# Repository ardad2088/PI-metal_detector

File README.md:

# Pulse Induction (PI) Metal Detector Board

2-layer mixed-signal PCB for a pulse induction metal detector: an STM32 microcontroller, a high-power MOSFET coil driver and an op-amp analog front end.

## How a PI detector works

A pulse induction detector drives its coil with short, strong current pulses and then looks at the signal that decays after each pulse. A metal target changes that decay, and the change is very small, so the receiving circuit has to amplify and condition it carefully before the microcontroller can use it.

## Hardware

| Block | Implementation |
|---|---|
| MCU | STM32F103C8T6 |
| Coil driver | High-power MOSFET switching stage with flyback diode protection for the inductive coil |
| Analog front end | Op-amp stages that amplify and condition the weak target reflection signal |
| Power | Linear regulation with capacitive noise filtering |
| Indicators | Audio and visual indicators |
| PCB | 2 layers, designed in [Altium Designer / KiCad] |

Schematic: [`docs/schematic.pdf`](docs/schematic.pdf) · PCB views: [`docs/pcb_top.png`](docs/pcb_top.png), [`docs/pcb_bottom.png`](docs/pcb_bottom.png)

## Repository layout

```
docs/       photos, schematic PDF, PCB renders
hardware/   KiCad project, libraries, Gerbers, BOM
```

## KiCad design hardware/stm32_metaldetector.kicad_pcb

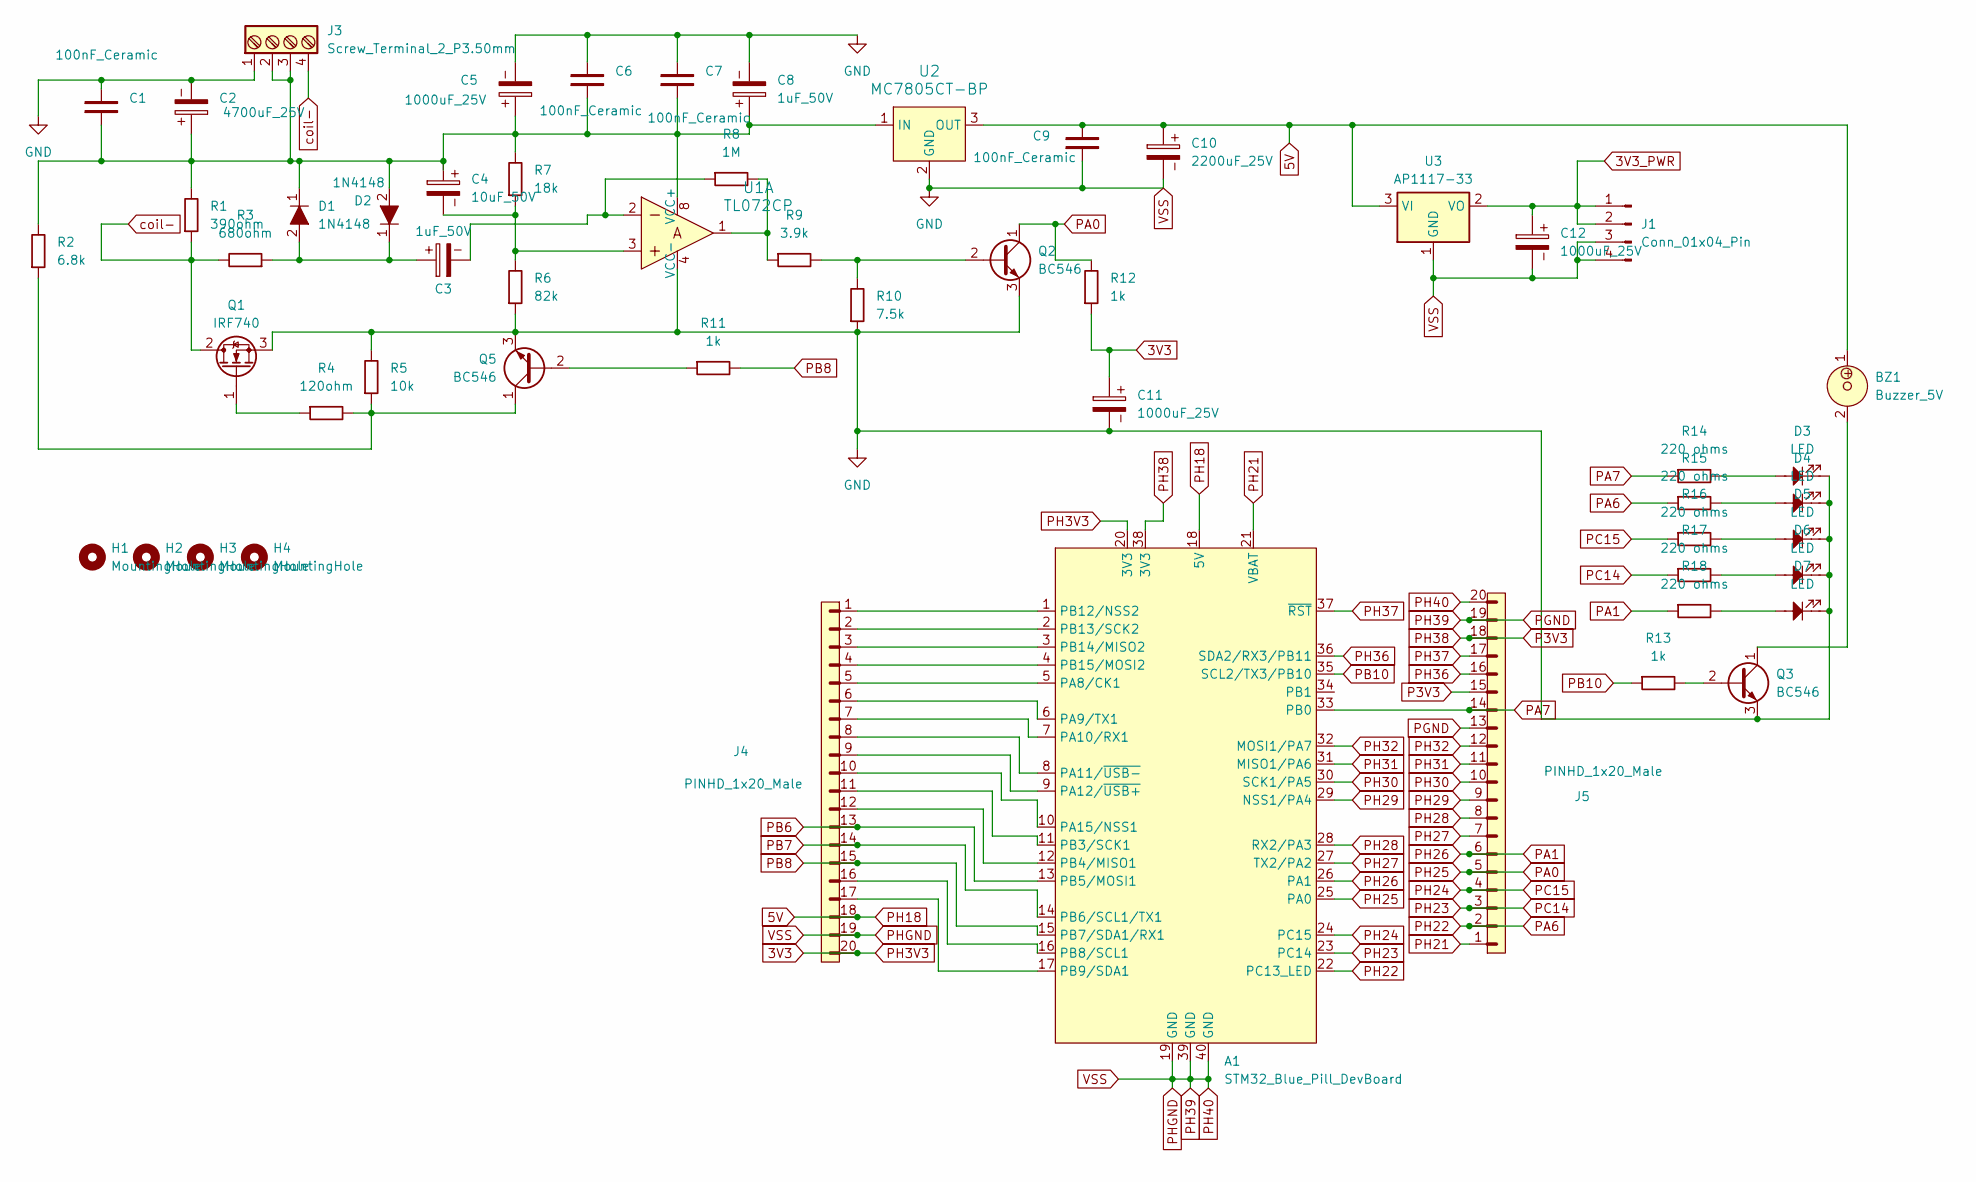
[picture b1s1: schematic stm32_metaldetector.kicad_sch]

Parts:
A1: STM32_Blue_Pill_DevBoard
BZ1: Buzzer_5V; MagneticBuzzer_ProSignal_ABT-410-RC
C1, C6, C7, C9: 100nF_Ceramic; C_Disc_D5.0mm_W2.5mm_P2.50mm
C2: 4700uF_25V; CP_Radial_D22.0mm_P10.00mm_SnapIn
C3, C8: 1uF_50V; CP_Radial_D5.0mm_P2.00mm
C4: 10uF_50V; CP_Radial_D5.0mm_P2.00mm
C5, C11: 1000uF_25V; CP_Radial_D13.0mm_P5.00mm
C10: 2200uF_25V; CP_Radial_D13.0mm_P5.00mm
C12: 1000uF_25V; CP_Radial_D8.0mm_P3.50mm
D1, D2: 1N4148; Diode_DO-35_P10mm; MPN 1N4148; Digi-Key_PN 1N4148FS-ND
D3, D4, D5, D6, D7: LED; LED_D5.0mm
H1, H2, H3, H4: MountingHole; MountingHole_4.3mm_M4
J1: Conn_01x04_Pin; PinHeader_1x04_P2.54mm_Vertical
J3: Screw_Terminal_2_P3.50mm; PhoenixContact_MC_1,5_4-G-3.81_1x04_P3.81mm_Horizontal
J4, J5: PINHD_1x20_Male; PinHeader_1x20_P2.54mm_Vertical
Q1: IRF740; TO-220-3_Vertical
Q2, Q3, Q5: BC546; TO-92_Inline
R1: 390ohm; R_Axial_DIN0617_L17.0mm_D6.0mm_P30.48mm_Horizontal
R2: 6.8k; R_Axial_DIN0207_L6.3mm_D2.5mm_P10.16mm_Horizontal
R3: 680ohm; R_Axial_DIN0411_L9.9mm_D3.6mm_P25.40mm_Horizontal
R4: 120ohm; R_Axial_DIN0207_L6.3mm_D2.5mm_P10.16mm_Horizontal
R5: 10k; R_Axial_DIN0207_L6.3mm_D2.5mm_P10.16mm_Horizontal
R6: 82k; R_Axial_DIN0207_L6.3mm_D2.5mm_P10.16mm_Horizontal
R7: 18k; R_Axial_DIN0207_L6.3mm_D2.5mm_P10.16mm_Horizontal
R8: 1M; R_Axial_DIN0207_L6.3mm_D2.5mm_P10.16mm_Horizontal
R9: 3.9k; R_Axial_DIN0207_L6.3mm_D2.5mm_P10.16mm_Horizontal
R10: 7.5k; R_Axial_DIN0207_L6.3mm_D2.5mm_P10.16mm_Horizontal
R11, R12, R13: 1k; R_Axial_DIN0207_L6.3mm_D2.5mm_P10.16mm_Horizontal
R14, R15, R16, R17, R18: 220 ohms; R_Axial_DIN0207_L6.3mm_D2.5mm_P10.16mm_Horizontal
U1: TL072CP; DIP-8_W7.62mm; MPN TL072CP; Digi-Key_PN 296-1775-5-ND
U2: MC7805CT-BP; TO-220-3; MPN MC7805CT-BP; Digi-Key_PN MC7805CT-BPMS-ND
U3: AP1117-33; SOT-223-3_TabPin2

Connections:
3V3: A1.20 (3V3), C11.1, J4.20, R12.1
3V3_PWR: C12.1, J1.1, J1.2, U3.2 (VO)
5V: A1.18 (5V), BZ1.1, C9.2, C10.1, J4.18, U2.3 (OUT), U3.3 (VI)
unnamed: A1.5 (PA8/CK1), J4.5
unnamed: A1.6 (PA9/TX1), J4.6
unnamed: A1.7 (PA10/RX1), J4.7
unnamed: A1.8 (PA11/~USB-), J4.8
unnamed: A1.9 (PA12/~USB+), J4.9
unnamed: A1.10 (PA15/NSS1), J4.10
unnamed: A1.11 (PB3/SCK1), J4.11
unnamed: A1.12 (PB4/MISO1), J4.12
unnamed: A1.16 (PB8/SCL1), J4.16
unnamed: A1.17 (PB9/SDA1), J4.17
unnamed: A1.1 (PB12/NSS2), J4.1
unnamed: A1.2 (PB13/SCK2), J4.2
unnamed: A1.3 (PB14/MISO2), J4.3
unnamed: A1.4 (PB15/MOSI2), J4.4
unnamed: C3.1, D1.2, D2.1, R3.1
unnamed: C3.2, R8.1, U1.2
unnamed: C4.2, R6.2, R7.1, U1.3
unnamed: D3.2, R14.2
unnamed: D4.2, R15.2
unnamed: D5.2, R16.2
unnamed: D6.2, R17.2
unnamed: D7.2, R18.2
unnamed: Q1.1 (G), R4.1
unnamed: Q2.2 (B), R9.2, R10.2
unnamed: Q3.2 (B), R13.2
unnamed: BZ1.2, Q3.1 (C)
unnamed: Q5.2 (B), R11.1
unnamed: Q5.1 (C), R2.1, R4.2, R5.1
unnamed: R8.2, R9.1, U1.1
unnamed: C1.1, C2.1, C4.1, C5.1, C6.1, C7.1, C8.1, D1.1, D2.2, J3.2, J3.3, R1.2, R2.2, R7.2, U1.8 (VCC+), U2.1 (IN)
P3V3: A1.38 (3V3), J5.15, J5.18
PA0: A1.25 (PA0), J5.5, Q2.1 (C), R12.2
PA1: A1.26 (PA1), J5.6, R18.1
PA6: A1.22 (PC13_LED), J5.2, R15.1
PA7: A1.33 (PB0), J5.14, R14.1
PB6: A1.13 (PB5/MOSI1), J4.13
PB7: A1.14 (PB6/SCL1/TX1), J4.14
PB8: A1.15 (PB7/SDA1/RX1), J4.15, R11.2
PB10: A1.35 (SCL2/TX3/PB10), R13.1
PC14: A1.23 (PC14), J5.3, R17.1
PC15: A1.24 (PC15), J5.4, R16.1
PGND: A1.19 (GND), A1.39 (GND), A1.40 (GND), C1.2, C2.2, C5.2, C6.2, C7.2, C8.2, C9.1, C10.2, C11.2, C12.2, D3.1, D4.1, D5.1, D6.1, D7.1, J1.3, J1.4, J3.1, J4.19, J5.13, J5.19, J5.20, Q1.3 (S), Q2.3 (E), Q3.3 (E), Q5.3 (E), R5.2, R6.1, R10.1, U1.4 (VCC-), U2.2 (GND), U3.1 (GND)
PH21: A1.21 (VBAT), J5.1
PH27: A1.27 (TX2/PA2), J5.7
PH28: A1.28 (RX2/PA3), J5.8
PH29: A1.29 (NSS1/PA4), J5.9
PH30: A1.30 (SCK1/PA5), J5.10
PH31: A1.31 (MISO1/PA6), J5.11
PH32: A1.32 (MOSI1/PA7), J5.12
PH36: A1.36 (SDA2/RX3/PB11), J5.16
PH37: A1.37 (~RST), J5.17
coil-: J3.4, Q1.2 (D), R1.1, R3.2

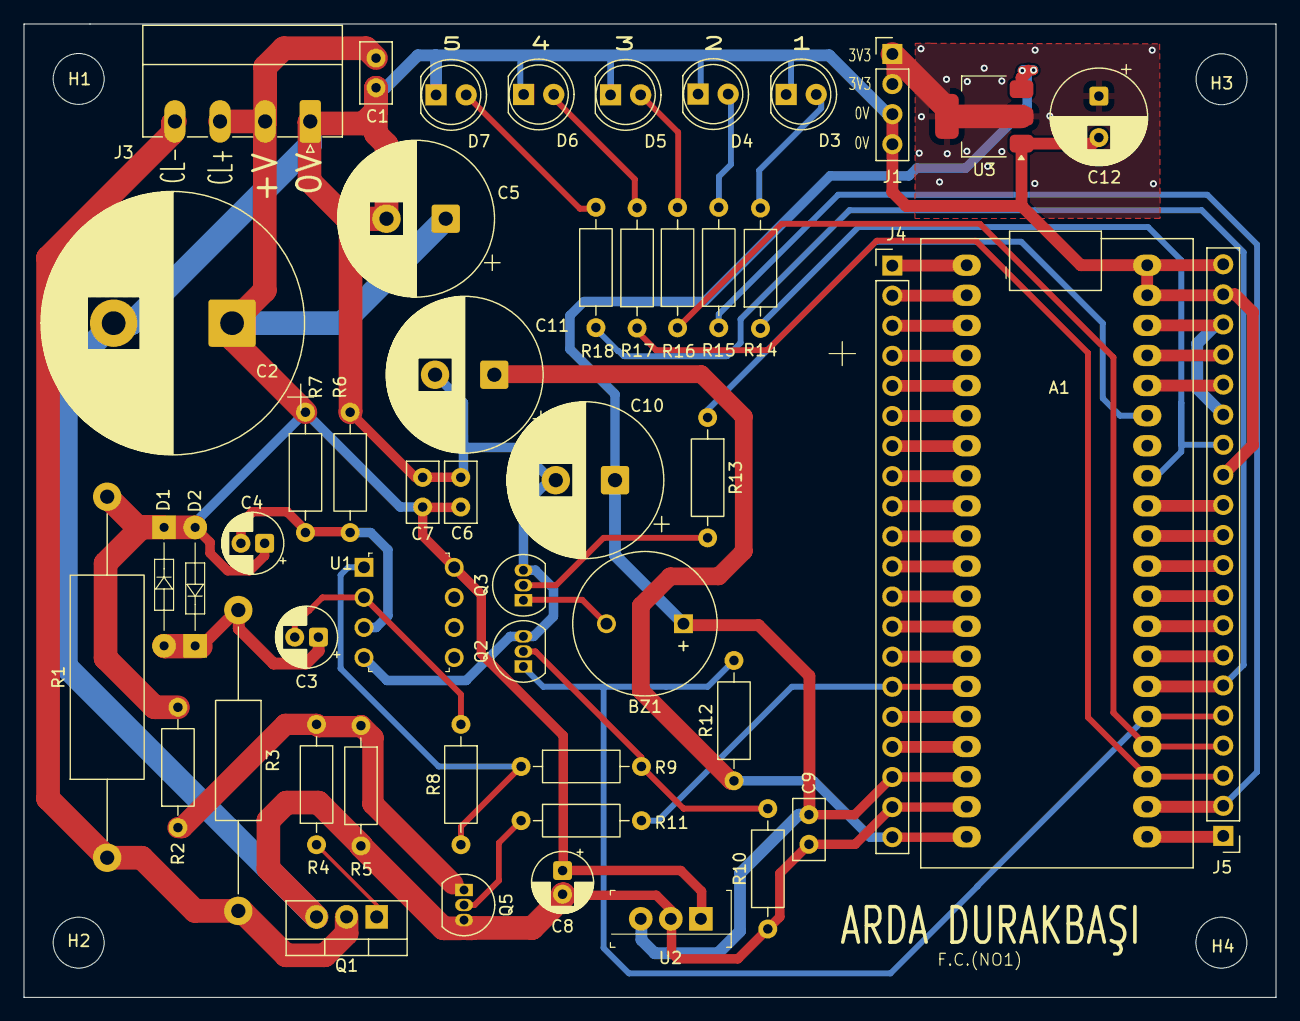
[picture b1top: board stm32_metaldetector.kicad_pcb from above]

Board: 2 copper layers, 105.7 x 82.2 mm, 54 parts (0 on the bottom side), 55 nets.
